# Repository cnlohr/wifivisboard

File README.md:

# wifivisboard

THIS REPO CONTAINS A REFERENCE IMPLEMENTATION FOR ESP-NOW ON THE ESP8266.  Also, previously "esp-freedom"

A project for a minimal reference swadge implemnetation.  

Specifically, this is being made for use with a sermonette for my youth group, to allow for "seeing" wifi. 
I did the initial design in about 2.5 hours on a flight from the hackaday supercon over twitter. 

https://twitter.com/cnlohr/status/1059287135319154688

I will be assembling the boards soon.

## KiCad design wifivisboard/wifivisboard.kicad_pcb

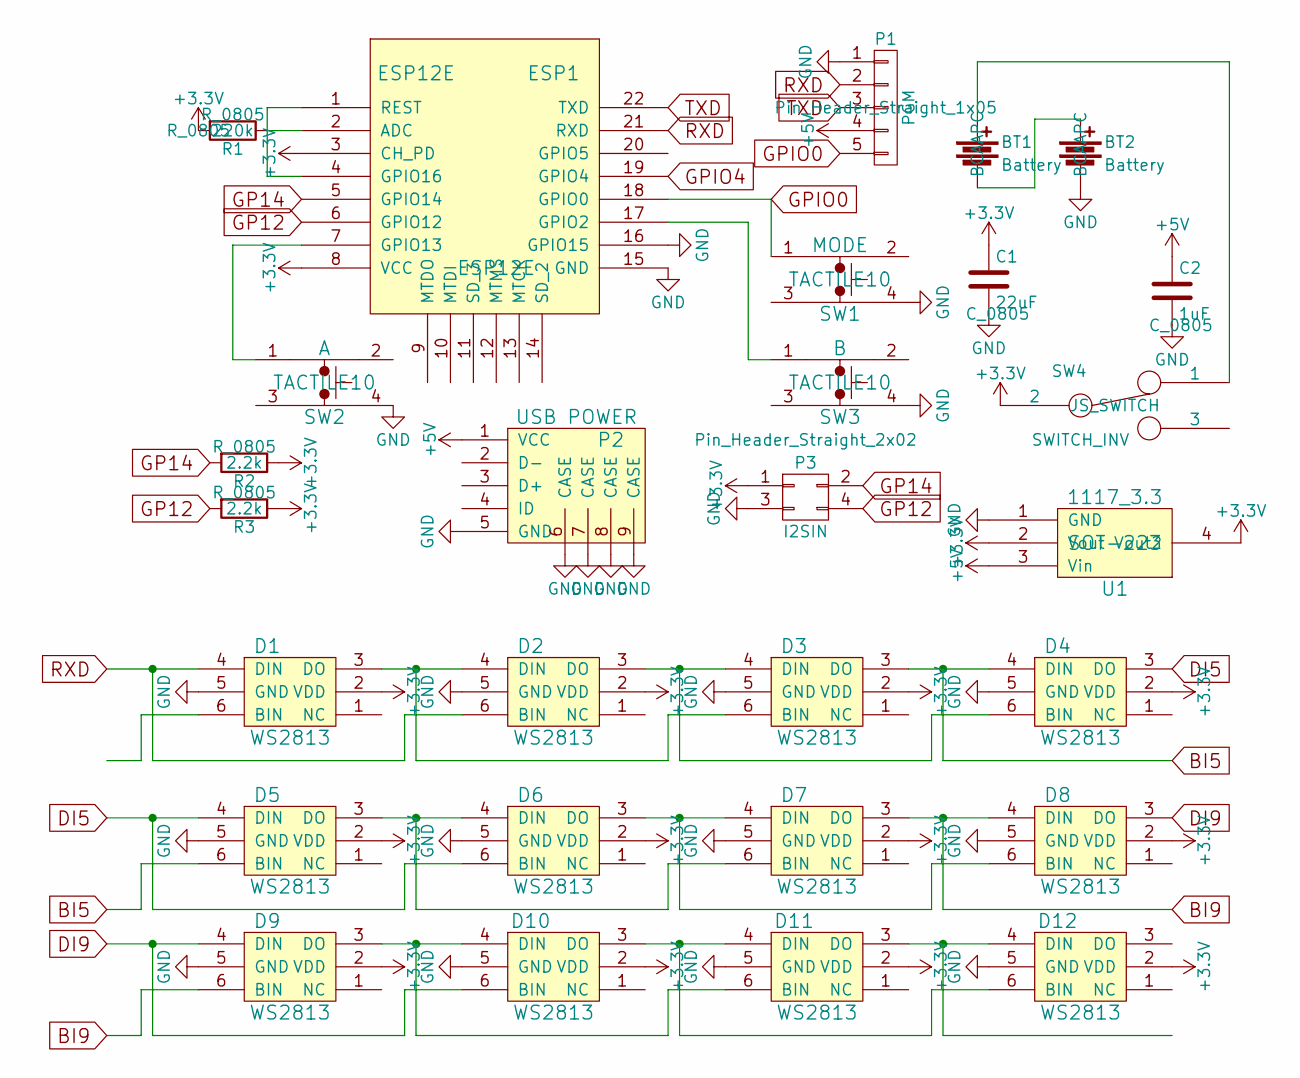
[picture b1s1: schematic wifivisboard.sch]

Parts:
BT1, BT2: Battery; BCAAPC
C1: 22uF; C_0805
C2: 1uF; C_0805
D1, D2, D3, D4, D5, D6, D7, D8, D9, D10, D11, D12: WS2813
ESP1: ESP12E
P1: PGM; Pin_Header_Straight_1x05
P2: USB POWER; USBMicroB-10118192-0001LF
P3: I2SIN; Pin_Header_Straight_2x02
R1: 220k; R_0805
R2, R3: 2.2k; R_0805
SW1: MODE; TACTILE10
SW2: A; TACTILE10
SW3: B; TACTILE10
SW4: SWITCH_INV; JS_SWITCH
U1: 1117_3.3; SOT-223

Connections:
+3V3: C1.1, D1.2 (VDD), D2.2 (VDD), D3.2 (VDD), D4.2 (VDD), D5.2 (VDD), D6.2 (VDD), D7.2 (VDD), D8.2 (VDD), D9.2 (VDD), D10.2 (VDD), D11.2 (VDD), D12.2 (VDD), ESP1.3 (CH_PD), ESP1.8 (VCC), P3.1, R1.2, R2.1, R3.1, SW4.2, U1.2 (Vout), U1.4 (Vout2)
+5V: C2.1, P1.4, P2.1 (VCC), U1.3 (Vin)
BI5: D3.3 (DO), D4.4 (DIN), D5.6 (BIN)
BI9: D7.3 (DO), D8.4 (DIN), D9.6 (BIN)
DI5: D4.3 (DO), D5.4 (DIN), D6.6 (BIN)
DI9: D8.3 (DO), D9.4 (DIN), D10.6 (BIN)
GND: BT2.2, C1.2, C2.2, D1.5 (GND), D2.5 (GND), D3.5 (GND), D4.5 (GND), D5.5 (GND), D6.5 (GND), D7.5 (GND), D8.5 (GND), D9.5 (GND), D10.5 (GND), D11.5 (GND), D12.5 (GND), ESP1.15 (GND), ESP1.16 (GPIO15), P1.1, P2.5 (GND), P2.6 (CASE), P2.7 (CASE), P2.8 (CASE), P2.9 (CASE), P3.3, SW1.4, SW2.4, SW3.4, U1.1 (GND)
GP12: ESP1.6 (GPIO12), P3.4, R3.2
GP14: ESP1.5 (GPIO14), P3.2, R2.2
GPIO0: ESP1.18 (GPIO0), P1.5, SW1.1
unnamed: BT1.1, SW4.1
unnamed: BT1.2, BT2.1
unnamed: D1.3 (DO), D2.4 (DIN), D3.6 (BIN)
unnamed: D2.3 (DO), D3.4 (DIN), D4.6 (BIN)
unnamed: D5.3 (DO), D6.4 (DIN), D7.6 (BIN)
unnamed: D6.3 (DO), D7.4 (DIN), D8.6 (BIN)
unnamed: D10.3 (DO), D11.4 (DIN), D12.6 (BIN)
unnamed: D9.3 (DO), D10.4 (DIN), D11.6 (BIN)
unnamed: D11.3 (DO), D12.4 (DIN)
unnamed: ESP1.1 (REST), ESP1.4 (GPIO16)
unnamed: ESP1.2 (ADC), R1.1
unnamed: ESP1.7 (GPIO13), SW2.1
unnamed: ESP1.17 (GPIO2), SW3.1
RXD: D1.4 (DIN), D2.6 (BIN), ESP1.21 (RXD), P1.2
TXD: ESP1.22 (TXD), P1.3

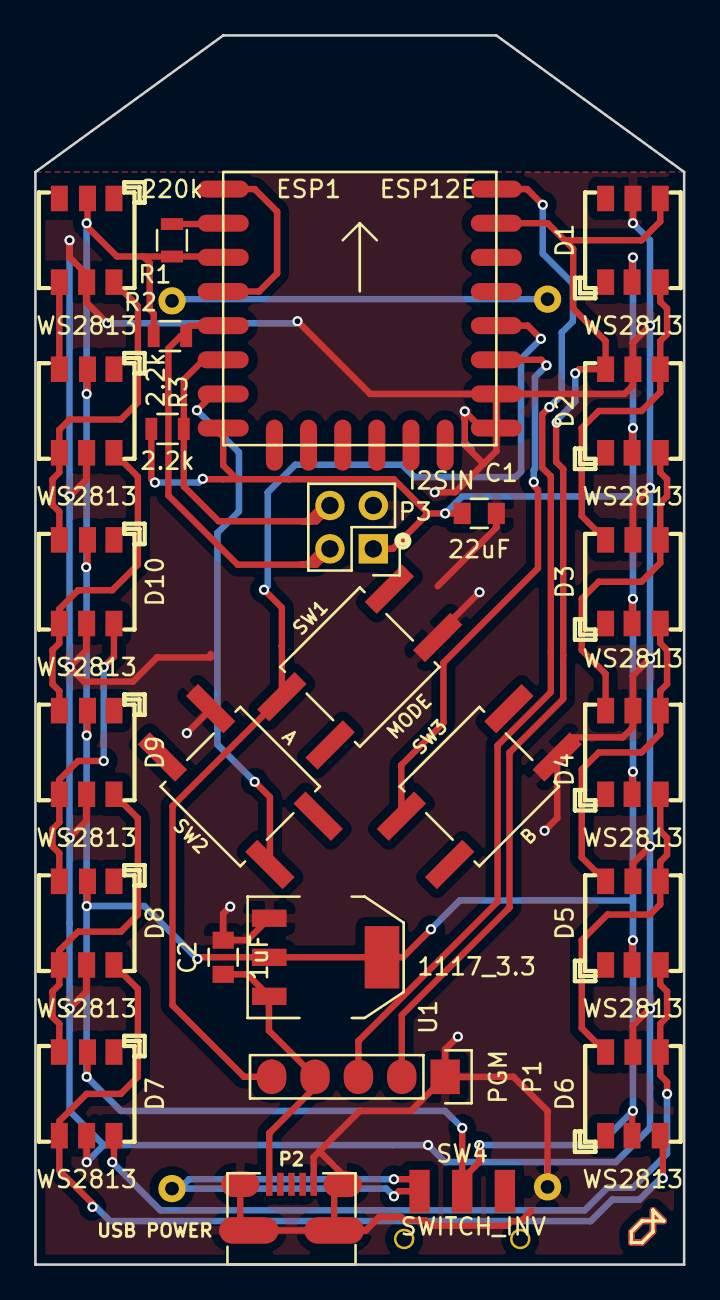
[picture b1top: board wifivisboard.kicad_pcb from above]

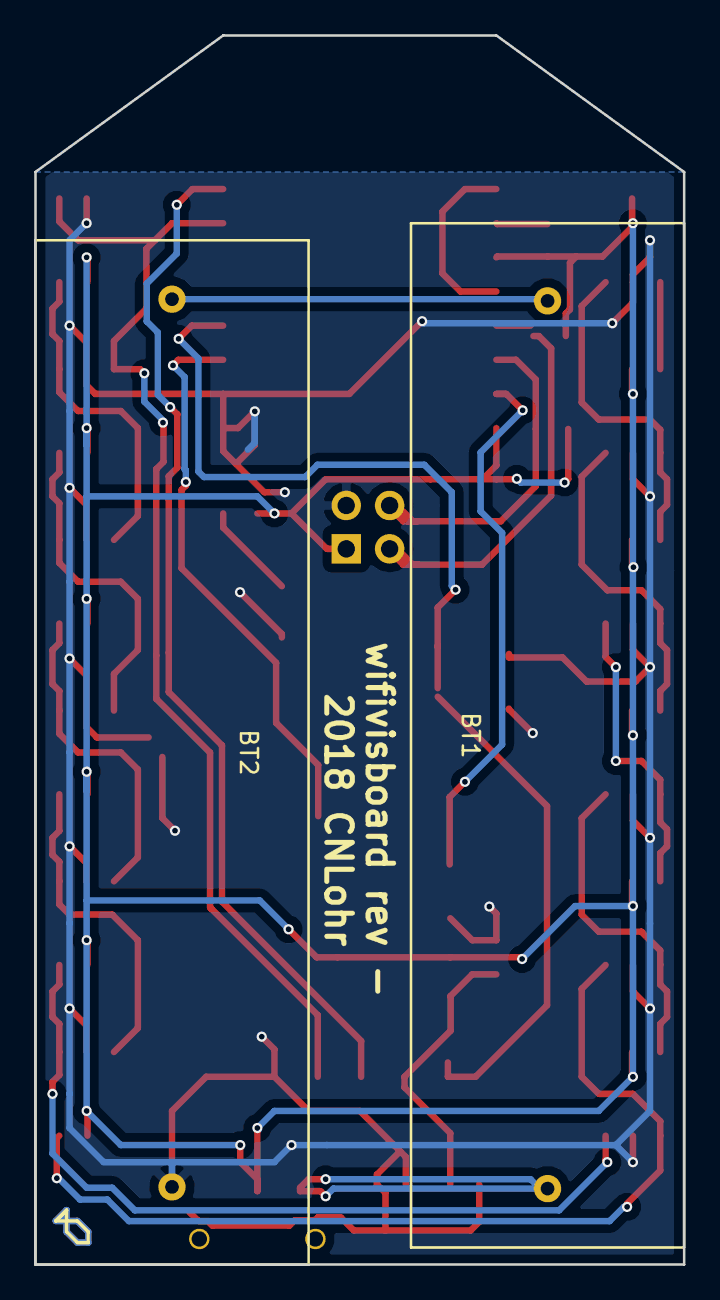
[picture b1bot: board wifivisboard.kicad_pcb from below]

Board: 2 copper layers, 38.0 x 72.0 mm, 28 parts (2 on the bottom side), 25 nets.

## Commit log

2018-11-05 Add design
2018-11-17 update design
2018-11-18 bump submodule
2018-11-18 update vis board slave object
2018-11-18 add basics
2018-11-18 add web
2018-11-18 add vis board
2018-11-19 add led tools
2018-11-19 bump codebase
2018-11-19 It's go time.
2018-11-19 add bins
2018-11-21 make firmware work with variable chip rates
2018-11-26 Update to what I tested against.
2018-11-27 update to allow users to become the central node.
